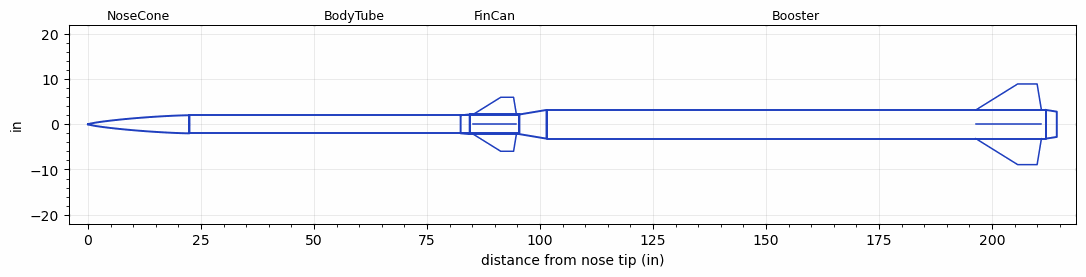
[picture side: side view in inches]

<RASAeroDocument>
 <FileVersion>2</FileVersion>
 <RocketDesign>
  <NoseCone>
   <Length>22.44</Length>
   <Diameter>4</Diameter>
   <Shape>Von Karman Ogive</Shape>
   <BluntRadius>0.0825</BluntRadius>
   <Location>0</Location>
  </NoseCone>
  <BodyTube>
   <Length>73</Length>
   <Diameter>4</Diameter>
   <Location>22.44</Location>
  </BodyTube>
  <FinCan>
   <Length>11</Length>
   <Diameter>4.35</Diameter>
   <InsideDiameter>4</InsideDiameter>
   <Location>95.44</Location>
   <ShoulderLength>2</ShoulderLength>
   <Offset>-11</Offset>
   <Fin>
    <Count>4</Count>
    <Chord>9.57</Chord>
    <Span>3.8</Span>
    <SweepDistance>6.105</SweepDistance>
    <TipChord>2.84</TipChord>
    <Thickness>0.25</Thickness>
    <LERadius>0.08</LERadius>
    <Location>10.23</Location>
    <AirfoilSection>Hexagonal</AirfoilSection>
    <FX1>0.5</FX1>
    <FX3>0.5</FX3>
   </Fin>
  </FinCan>
  <Booster>
   <Length>110.5</Length>
   <Diameter>6.35</Diameter>
   <InsideDiameter>4.35</InsideDiameter>
   <Location>95.44</Location>
   <ShoulderLength>6</ShoulderLength>
   <BoattailLength>2.4</BoattailLength>
   <BoattailRearDiameter>5.6</BoattailRearDiameter>
   <Fin>
    <Count>4</Count>
    <Chord>14.5</Chord>
    <Span>5.75</Span>
    <SweepDistance>9.25</SweepDistance>
    <TipChord>4.3</TipChord>
    <Thickness>0.25</Thickness>
    <LERadius>0.08</LERadius>
    <Location>15.5</Location>
    <AirfoilSection>Hexagonal</AirfoilSection>
    <FX1>0.5</FX1>
    <FX3>0.5</FX3>
   </Fin>
  </Booster>
  <Surface>Cast Iron (Very Rough)</Surface>
  <ModifiedBarrowman>True</ModifiedBarrowman>
  <Turbulence>True</Turbulence>
  <UseBooster1>False</UseBooster1>
  <UseBooster2>False</UseBooster2>
 </RocketDesign>
 <LaunchSite>
  <Altitude>3000</Altitude>
  <Pressure>0</Pressure>
  <RodAngle>2</RodAngle>
  <RodLength>18</RodLength>
  <Temperature>85</Temperature>
  <WindSpeed>8</WindSpeed>
 </LaunchSite>
 <Recovery>
  <Altitude1>1000</Altitude1>
  <Altitude2>1000</Altitude2>
  <DeviceType1>None</DeviceType1>
  <DeviceType2>None</DeviceType2>
  <Event1>False</Event1>
  <Event2>False</Event2>
  <Size1>1</Size1>
  <Size2>1</Size2>
  <EventType1>None</EventType1>
  <EventType2>None</EventType2>
  <CD1>1.33</CD1>
  <CD2>1.33</CD2>
 </Recovery>
 <SimulationList>
  <Simulation>
   <SustainerEngine>O5100  (O5100)</SustainerEngine>
   <SustainerLaunchWt>55.5</SustainerLaunchWt>
   <SustainerNozzleDiameter>3.8</SustainerNozzleDiameter>
   <SustainerCG>55.25</SustainerCG>
   <SustainerIgnitionDelay>15</SustainerIgnitionDelay>
   <Booster1Engine>Q10000  (Q10000)</Booster1Engine>
   <Booster1LaunchWt>214.3</Booster1LaunchWt>
   <Booster1SeparationDelay>0</Booster1SeparationDelay>
   <Booster1IgnitionDelay>0</Booster1IgnitionDelay>
   <Booster1CG>119.51</Booster1CG>
   <Booster1NozzleDiameter>5.3</Booster1NozzleDiameter>
   <IncludeBooster1>True</IncludeBooster1>
   <Booster2Delay>0</Booster2Delay>
   <IncludeBooster2>False</IncludeBooster2>
   <TimetoApogee>210.2886</TimetoApogee>
   <MaxAltitude>588914.8</MaxAltitude>
   <MaxVelocity>6270.047</MaxVelocity>
  </Simulation>
 </SimulationList>
</RASAeroDocument>
